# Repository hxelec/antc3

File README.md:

These are the files for the 150g antweight combat robot I recently made. I made an all-in-one robot controller, which is, in my opinion, a better alternative to the Malenki-Nano and Malenki-HV, and a very low-cost ESP-NOW remote. The high-quality PCBs for this project were manufactured by PCBWay, and if you use my link to sign up: https://pcbway.com/g/x5f10h, you can get $5 off your first order and help support this (partially) open-source development. You can check out the video for this project on my YouTube channel: https://youtube.com/@hxtec32?si=qvrlxVD-KIIIB9TC
The code does not have failsafe, and doesn't drive the robot fully straight by the way, but feel free to use it as a reference for bidirectional ESP-NOW communication. I would recommend reading this article too, as I adapted the code for my own use case: https://randomnerdtutorials.com/esp-now-two-way-communication-esp32/
By the way, you need the necessary Arduino files for a T-QT Pro before using my code, because it won't work if otherwise. The T-QT Pro is great for this project.

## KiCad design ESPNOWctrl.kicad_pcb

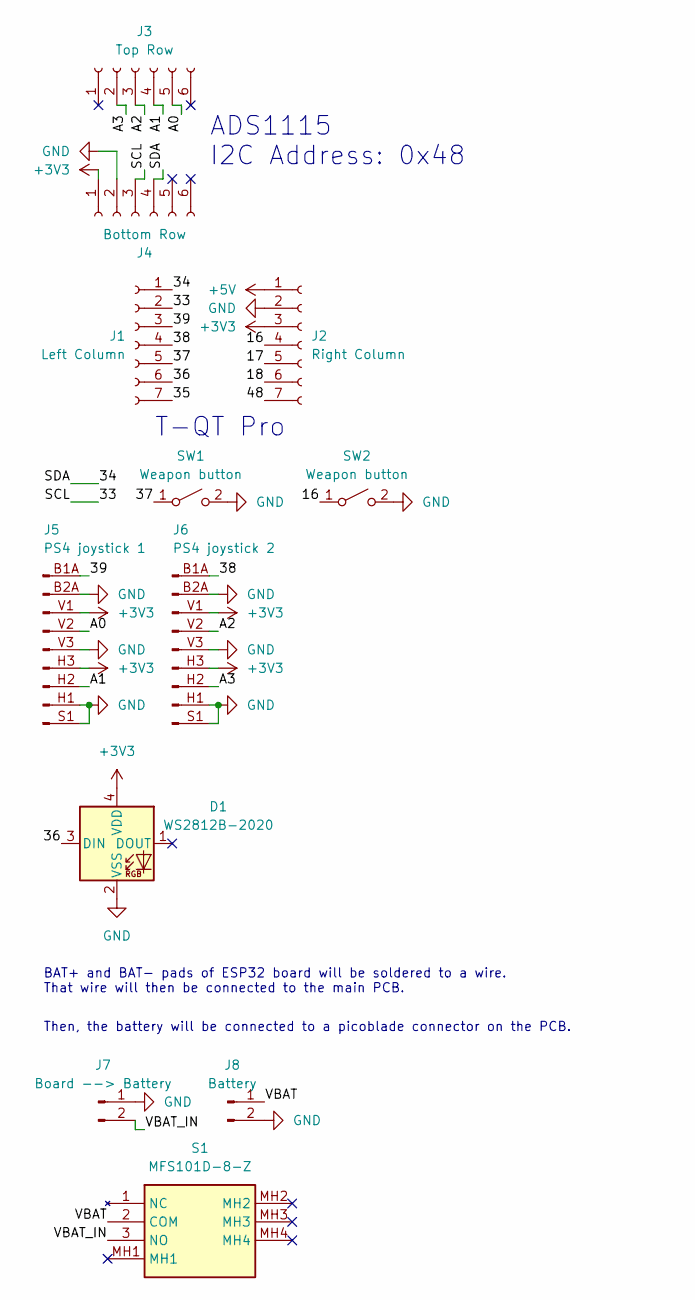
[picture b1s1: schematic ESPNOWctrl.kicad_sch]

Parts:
D1: WS2812B-2020; LED_WS2812B-2020_PLCC4_2.0x2.0mm
J1: Left Column; PinSocket_1x07_P2.54mm_Vertical
J2: Right Column; PinSocket_1x07_P2.54mm_Vertical
J3: Top Row; PinSocket_1x06_P2.54mm_Vertical
J4: Bottom Row; PinSocket_1x06_P2.54mm_Vertical
J5: PS4 joystick 1; PS4_joystick
J6: PS4 joystick 2; PS4_joystick
J7: Board --> Battery; JST_PH_B2B-PH-K_1x02_P2.00mm_Vertical
J8: Battery; JST_PH_B2B-PH-K_1x02_P2.00mm_Vertical
S1: MFS101D-8-Z; MFS101D8Z; Manufacturer_Part_Number MFS101D-8-Z
SW1, SW2: Weapon button; SW_SPST_Omron_B3F-315x_Angled

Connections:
+3V3: D1.4 (VDD), J2.3, J4.1, J5.H3 (Pin_6), J5.V1 (Pin_3), J6.H3 (Pin_6), J6.V1 (Pin_3)
+5V: J2.1
/16: J2.4, SW2.1 (A)
/17: J2.5
/18: J2.6
/33: J1.2, J4.3
/34: J1.1, J4.4
/35: J1.7
/36: D1.3 (DIN), J1.6
/37: J1.5, SW1.1 (A)
/38: J1.4, J6.B1A (Pin_1), J6.B1B (Pin_1)
/39: J1.3, J5.B1A (Pin_1), J5.B1B (Pin_1)
/48: J2.7
/A0: J3.5, J5.V2 (Pin_4)
/A1: J3.4, J5.H2 (Pin_7)
/A2: J3.3, J6.V2 (Pin_4)
/A3: J3.2, J6.H2 (Pin_7)
/VBAT: J8.1, S1.2 (COM)
/VBAT_IN: J7.2, S1.3 (NO)
GND: D1.2 (VSS), J2.2, J4.2, J5.B2A (Pin_2), J5.B2B (Pin_2), J5.H1 (Pin_8), J5.S1 (Pin_9), J5.S2 (Pin_9), J5.S3 (Pin_9), J5.S4 (Pin_9), J5.V3 (Pin_5), J6.B2A (Pin_2), J6.B2B (Pin_2), J6.H1 (Pin_8), J6.S1 (Pin_9), J6.S2 (Pin_9), J6.S3 (Pin_9), J6.S4 (Pin_9), J6.V3 (Pin_5), J7.1, J8.2, SW1.2 (B), SW2.2 (B)

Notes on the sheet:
T-QT Pro
ADS1115 I2C Address: 0x48
BAT+ and BAT- pads of ESP32 board will be soldered to a wire. That wire will then be connected to the main PCB.
Then, the battery will be connected to a picoblade connector on the PCB.

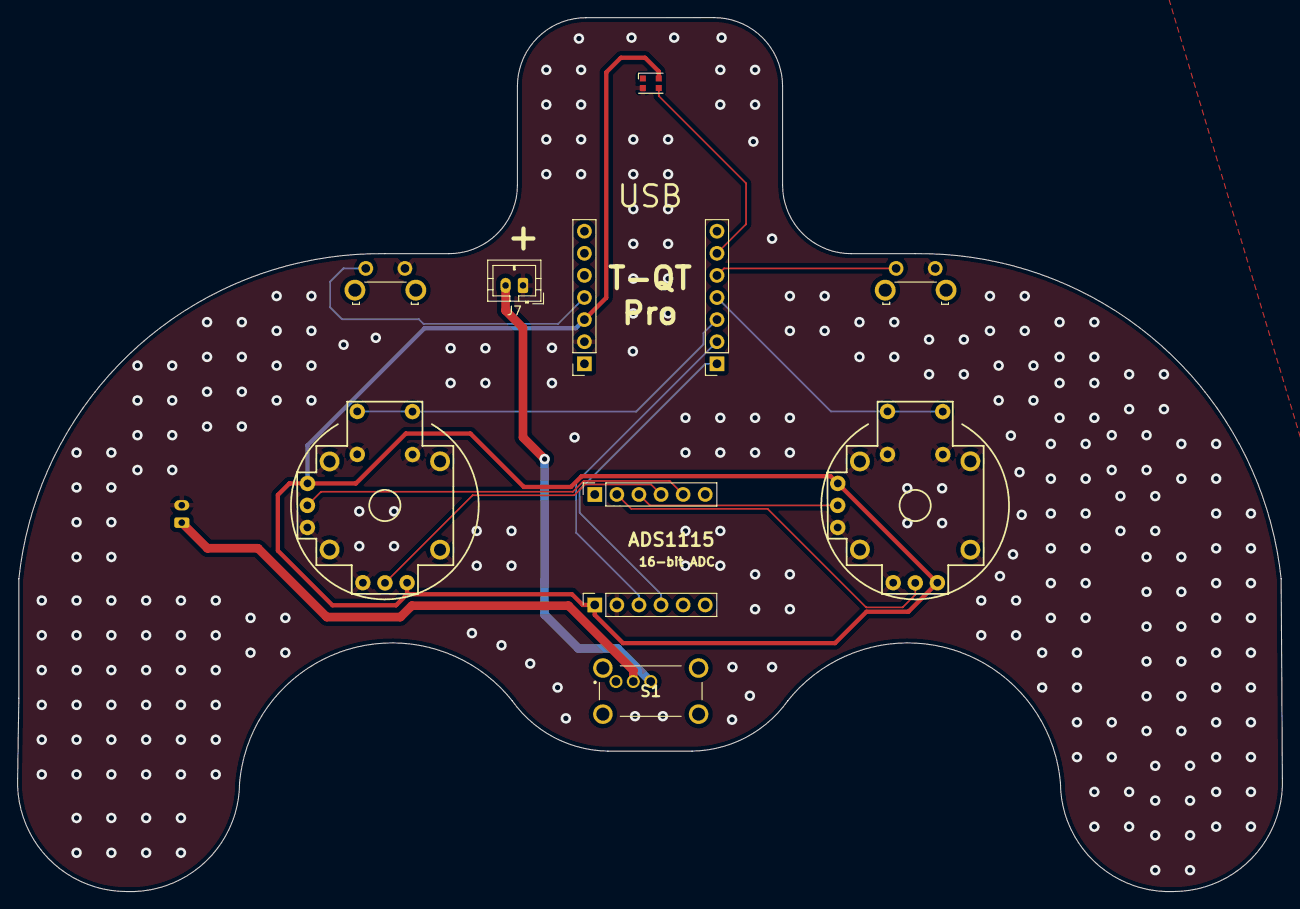
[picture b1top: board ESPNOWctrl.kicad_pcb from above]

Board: 2 copper layers, 145.4 x 100.5 mm, 12 parts (1 on the bottom side), 15 nets.

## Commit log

2024-04-02 Create LICENSE
2024-04-03 Arduino sketches for ESP-NOW communication
    this isn't done yet, I don't recommend using it lol
